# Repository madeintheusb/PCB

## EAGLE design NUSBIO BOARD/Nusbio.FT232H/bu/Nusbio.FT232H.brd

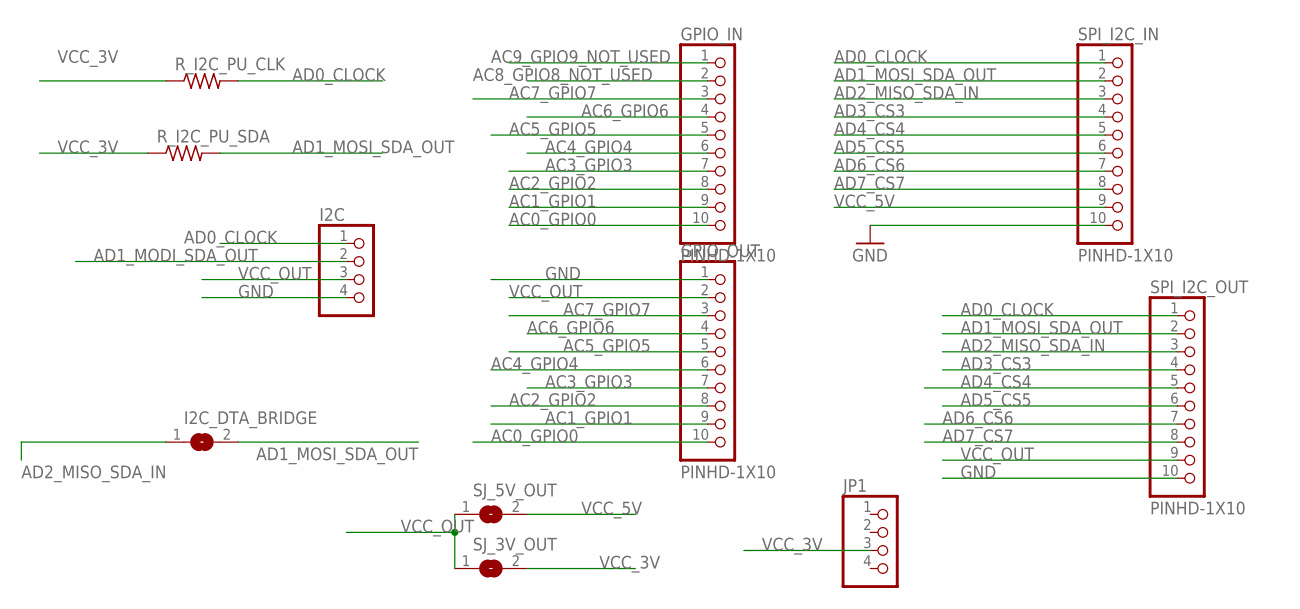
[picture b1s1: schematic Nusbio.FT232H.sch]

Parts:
GPIO_IN: PINHD-1X10; 1X10-BIG
GPIO_OUT: PINHD-1X10; 1X10-BIG
I2C: PINHD-1X4; 1X04
I2C_DTA_BRIDGE: SOLDERJUMPERREFLOW; SOLDERJUMPER_REFLOW
JP1: PINHD-1X4; 1X04
R_I2C_PU_CLK, R_I2C_PU_SDA: R-US_R1206; R1206
SJ_3V_OUT, SJ_5V_OUT: SOLDERJUMPERREFLOW; SOLDERJUMPER_REFLOW
SPI_I2C_IN, SPI_I2C_OUT: PINHD-1X10; 1X10-BIG

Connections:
AC0_GPIO0: GPIO_IN.10, GPIO_OUT.10
AC1_GPIO1: GPIO_IN.9, GPIO_OUT.9
AC2_GPIO2: GPIO_IN.8, GPIO_OUT.8
AC3_GPIO3: GPIO_IN.7, GPIO_OUT.7
AC4_GPIO4: GPIO_IN.6, GPIO_OUT.6
AC5_GPIO5: GPIO_IN.5, GPIO_OUT.5
AC6_GPIO6: GPIO_IN.4, GPIO_OUT.4
AC7_GPIO7: GPIO_IN.3, GPIO_OUT.3
AC8_GPIO8_NOT_USED: GPIO_IN.2
AC9_GPIO9_NOT_USED: GPIO_IN.1
AD0_CLOCK: I2C.1, R_I2C_PU_CLK.2, SPI_I2C_IN.1, SPI_I2C_OUT.1
AD1_MODI_SDA_OUT: I2C.2
AD1_MOSI_SDA_OUT: I2C_DTA_BRIDGE.2, R_I2C_PU_SDA.2, SPI_I2C_IN.2, SPI_I2C_OUT.2
AD2_MISO_SDA_IN: I2C_DTA_BRIDGE.1, SPI_I2C_IN.3, SPI_I2C_OUT.3
AD3_CS3: SPI_I2C_IN.4, SPI_I2C_OUT.4
AD4_CS4: SPI_I2C_IN.5, SPI_I2C_OUT.5
AD5_CS5: SPI_I2C_IN.6, SPI_I2C_OUT.6
AD6_CS6: SPI_I2C_IN.7, SPI_I2C_OUT.7
AD7_CS7: SPI_I2C_IN.8, SPI_I2C_OUT.8
GND: GPIO_OUT.1, I2C.4, SPI_I2C_IN.10, SPI_I2C_OUT.10
VCC_3V: JP1.3, R_I2C_PU_CLK.1, R_I2C_PU_SDA.1, SJ_3V_OUT.2
VCC_5V: SJ_5V_OUT.2, SPI_I2C_IN.9
VCC_OUT: GPIO_OUT.2, I2C.3, SJ_3V_OUT.1, SJ_5V_OUT.1, SPI_I2C_OUT.9

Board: 2 copper layers, 11 parts (0 on the bottom side), 20 nets, no tracks yet.

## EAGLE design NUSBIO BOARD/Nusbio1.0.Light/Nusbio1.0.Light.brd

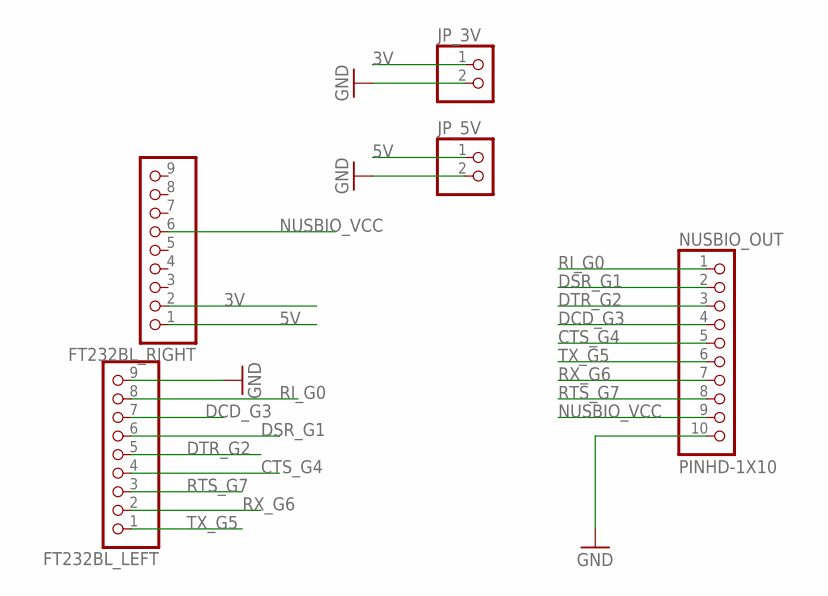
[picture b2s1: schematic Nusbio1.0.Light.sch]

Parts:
FT232BL_LEFT, FT232BL_RIGHT: PINHD-1X9; 1X09-BIG
JP_3V, JP_5V: PINHD-1X2; 1X02
NUSBIO_OUT: PINHD-1X10; 1X10-BIG

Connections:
3V: FT232BL_RIGHT.2, JP_3V.1
5V: FT232BL_RIGHT.1, JP_5V.1
CTS_G4: FT232BL_LEFT.4, NUSBIO_OUT.5
DCD_G3: FT232BL_LEFT.7, NUSBIO_OUT.4
DSR_G1: FT232BL_LEFT.6, NUSBIO_OUT.2
DTR_G2: FT232BL_LEFT.5, NUSBIO_OUT.3
GND: FT232BL_LEFT.9, JP_3V.2, JP_5V.2, NUSBIO_OUT.10
NUSBIO_VCC: FT232BL_RIGHT.6, NUSBIO_OUT.9
RI_G0: FT232BL_LEFT.8, NUSBIO_OUT.1
RTS_G7: FT232BL_LEFT.3, NUSBIO_OUT.8
RX_G6: FT232BL_LEFT.2, NUSBIO_OUT.7
TX_G5: FT232BL_LEFT.1, NUSBIO_OUT.6

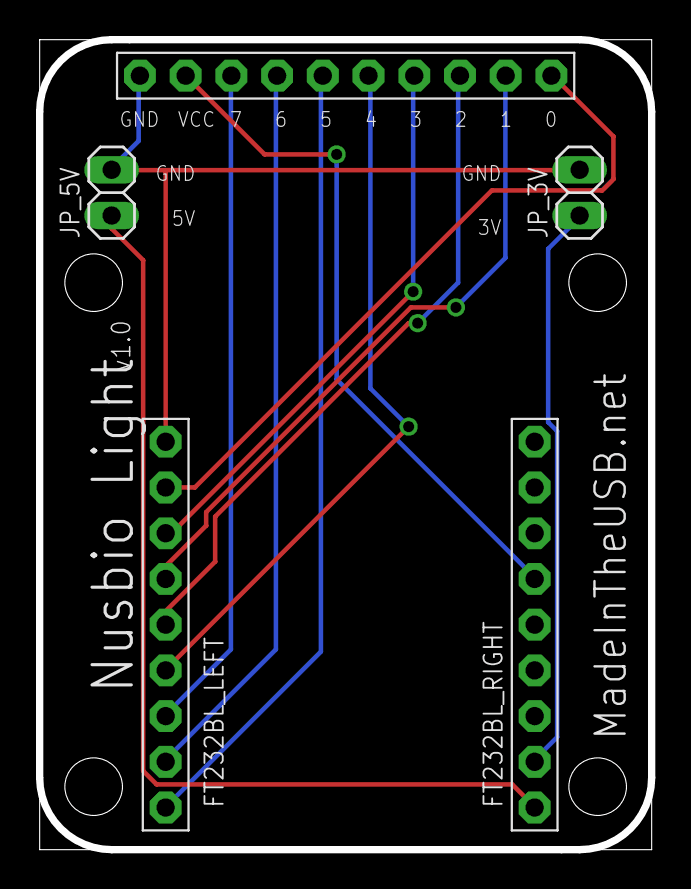
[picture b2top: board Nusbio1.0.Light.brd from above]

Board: 2 copper layers, 34.0 x 45.0 mm, 5 parts (0 on the bottom side), 12 nets.

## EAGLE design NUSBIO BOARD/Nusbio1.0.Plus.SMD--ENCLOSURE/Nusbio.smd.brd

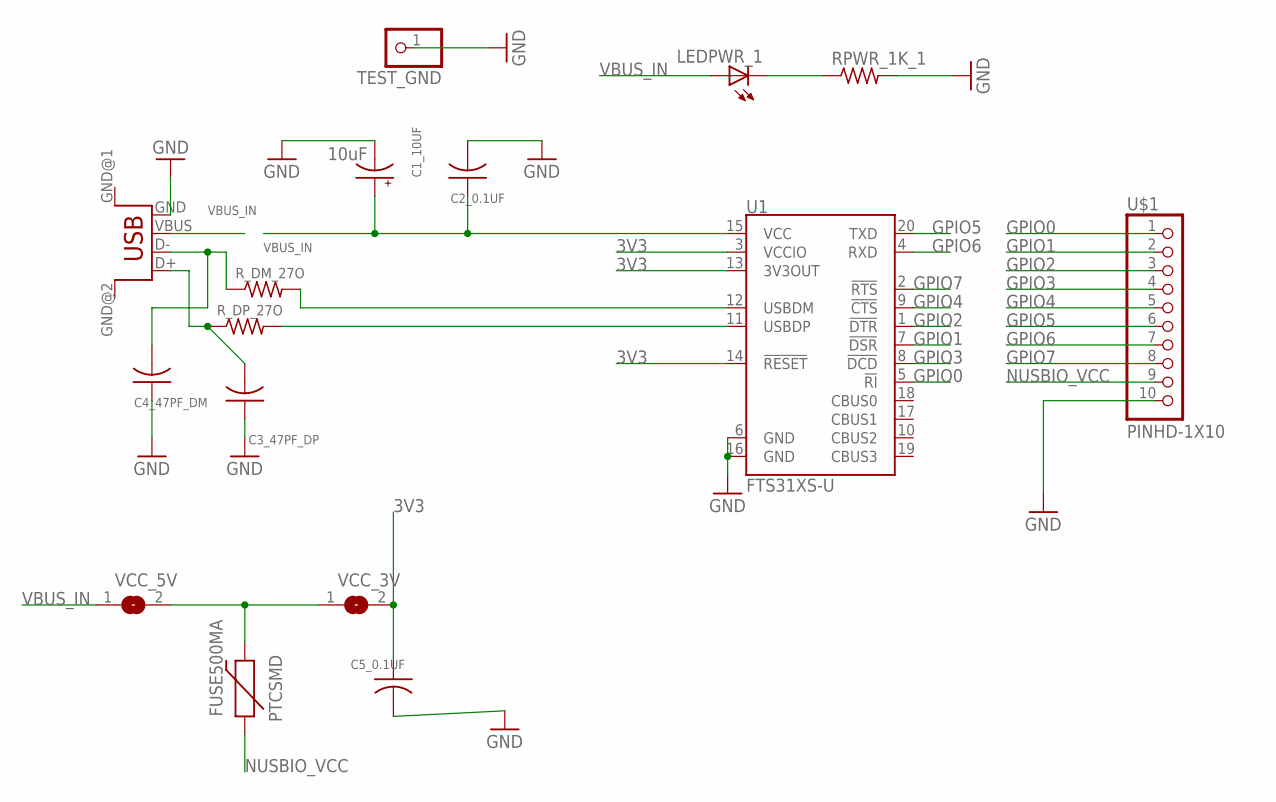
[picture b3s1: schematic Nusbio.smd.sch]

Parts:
C1_10UF: 10uF; EIA3216
C2_0.1UF, C3_47PF_DP, C4_47PF_DM, C5_0.1UF: C-USC1206; C1206
FUSE500MA: PTCSMD; PTC-1206
LEDPWR_1: LEDCHIPLED_0805; CHIPLED_0805
RPWR_1K_1: R-US_R0805; R0805
R_DM_27O: R-US_R0805; R0805
R_DP_27O: R-US_R0805; R0805
TEST_GND: PINHD-1X1; 1X01
U1: FTS31XS-U; SSOP20_L
U$1: PINHD-1X10; 1X10-BIG
USB_FEMALE: USB; USB-FEMALE-A-PTH
VCC_3V, VCC_5V: SOLDERJUMPERREFLOW; SOLDERJUMPER_REFLOW

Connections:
3V3: C5_0.1UF.1, U1.3 (VCCIO), U1.13 (3V3OUT), U1.14 (!RESET), VCC_3V.2
GND: C1_10UF.C (-), C2_0.1UF.2, C3_47PF_DP.1, C4_47PF_DM.1, C5_0.1UF.2, RPWR_1K_1.2, TEST_GND.1, U1.6 (GND), U1.16 (GND), U$1.10, USB_FEMALE.GND
GPIO0: U1.5 (!RI), U$1.1
GPIO1: U1.7 (!DSR), U$1.2
GPIO2: U1.1 (!DTR), U$1.3
GPIO3: U1.8 (!DCD), U$1.4
GPIO4: U1.9 (!CTS), U$1.5
GPIO5: U1.20 (TXD), U$1.6
GPIO6: U1.4 (RXD), U$1.7
GPIO7: U1.2 (!RTS), U$1.8
unnamed: LEDPWR_1.C, RPWR_1K_1.1
unnamed: R_DM_27O.2, U1.12 (USBDM)
unnamed: R_DP_27O.2, U1.11 (USBDP)
unnamed: FUSE500MA.2, VCC_3V.1, VCC_5V.2
unnamed: C3_47PF_DP.2, R_DP_27O.1, USB_FEMALE.D+
unnamed: C4_47PF_DM.2, R_DM_27O.1, USB_FEMALE.D-
NUSBIO_VCC: FUSE500MA.1, U$1.9
VBUS_IN: C1_10UF.A (+), C2_0.1UF.1, LEDPWR_1.A, U1.15 (VCC), USB_FEMALE.VBUS, VCC_5V.1

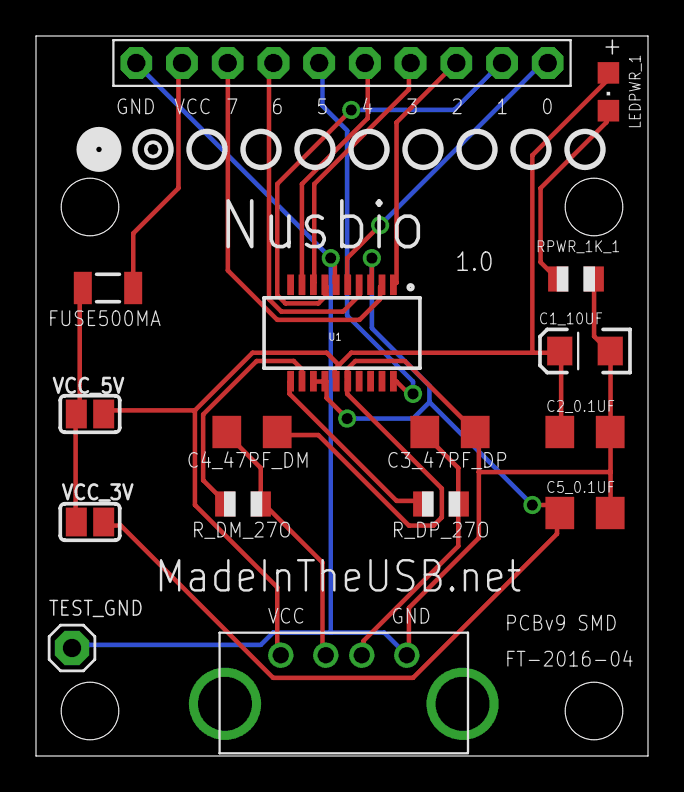
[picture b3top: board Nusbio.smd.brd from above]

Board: 2 copper layers, 34.0 x 40.0 mm, 16 parts (0 on the bottom side), 18 nets.

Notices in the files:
parts and their libraries:
microbuilder: This work is placed in the public domain, and may be freely used for commercial and non-commercial work with the following conditions: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
SparkFun-Capacitors: Licensing: Creative Commons ShareAlike 4.0 International - https://creativecommons.org/licenses/by-sa/4.0
